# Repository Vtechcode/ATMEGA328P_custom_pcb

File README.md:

# ATMEGA328P CUSTOM PCB

A custom development board based on the ATMEGA328P chip

## Features
ATMEGA328P MCU

## Preview

## Schematic

## PCB Layout

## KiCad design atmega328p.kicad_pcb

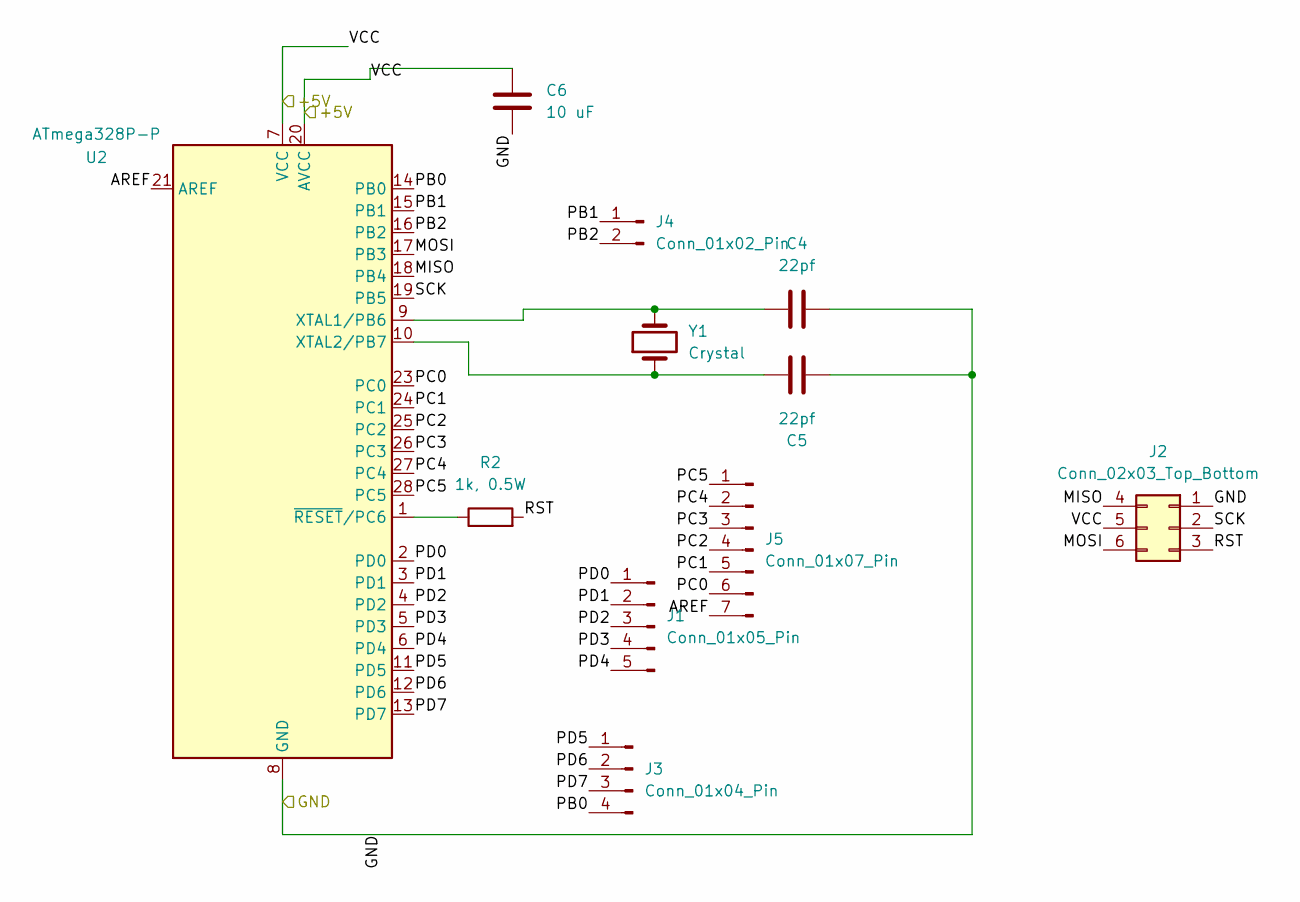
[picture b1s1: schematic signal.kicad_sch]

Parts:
C4, C5: 22pf; C_Disc_D3.8mm_W2.6mm_P2.50mm
C6: 10 uF; C_Disc_D6.0mm_W2.5mm_P5.00mm
J1: Conn_01x05_Pin; PinSocket_1x05_P2.54mm_Vertical
J2: Conn_02x03_Top_Bottom; PinSocket_2x03_P2.54mm_Vertical
J3: Conn_01x04_Pin; PinHeader_1x04_P2.54mm_Vertical
J4: Conn_01x02_Pin; PinHeader_1x02_P2.54mm_Vertical
J5: Conn_01x07_Pin; PinHeader_1x07_P2.54mm_Vertical
R2: 1k, 0.5W; R_Axial_DIN0207_L6.3mm_D2.5mm_P10.16mm_Horizontal
U2: ATmega328P-P; DIP-28_W7.62mm
Y1: Crystal; Crystal_HC18-U_Vertical

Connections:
/power/+5V: C6.1, J2.5, U2.7 (VCC), U2.20 (AVCC); also elsewhere on the board
/signal/AREF: J5.7, U2.21 (AREF)
/signal/GND: C4.2, C5.2, C6.2, J2.1, U2.8 (GND), U2.22 (GND); also elsewhere on the board
/signal/MISO: J2.4, U2.18 (PB4)
/signal/MOSI: J2.6, U2.17 (PB3)
/signal/PB0: J3.4, U2.14 (PB0)
/signal/PB1: J4.1, U2.15 (PB1)
/signal/PB2: J4.2, U2.16 (PB2)
/signal/PC0: J5.6, U2.23 (PC0)
/signal/PC1: J5.5, U2.24 (PC1)
/signal/PC2: J5.4, U2.25 (PC2)
/signal/PC3: J5.3, U2.26 (PC3)
/signal/PC4: J5.2, U2.27 (PC4)
/signal/PC5: J5.1, U2.28 (PC5)
/signal/PD0: J1.1, U2.2 (PD0)
/signal/PD1: J1.2, U2.3 (PD1)
/signal/PD2: J1.3, U2.4 (PD2)
/signal/PD3: J1.4, U2.5 (PD3)
/signal/PD4: J1.5, U2.6 (PD4)
/signal/PD5: J3.1, U2.11 (PD5)
/signal/PD6: J3.2, U2.12 (PD6)
/signal/PD7: J3.3, U2.13 (PD7)
/signal/RST: J2.3, R2.2
/signal/SCK: J2.2, U2.19 (PB5)
unnamed: C4.1, U2.9 (XTAL1/PB6), Y1.2
unnamed: C5.1, U2.10 (XTAL2/PB7), Y1.1
unnamed: R2.1, U2.1 (~RESET/PC6)

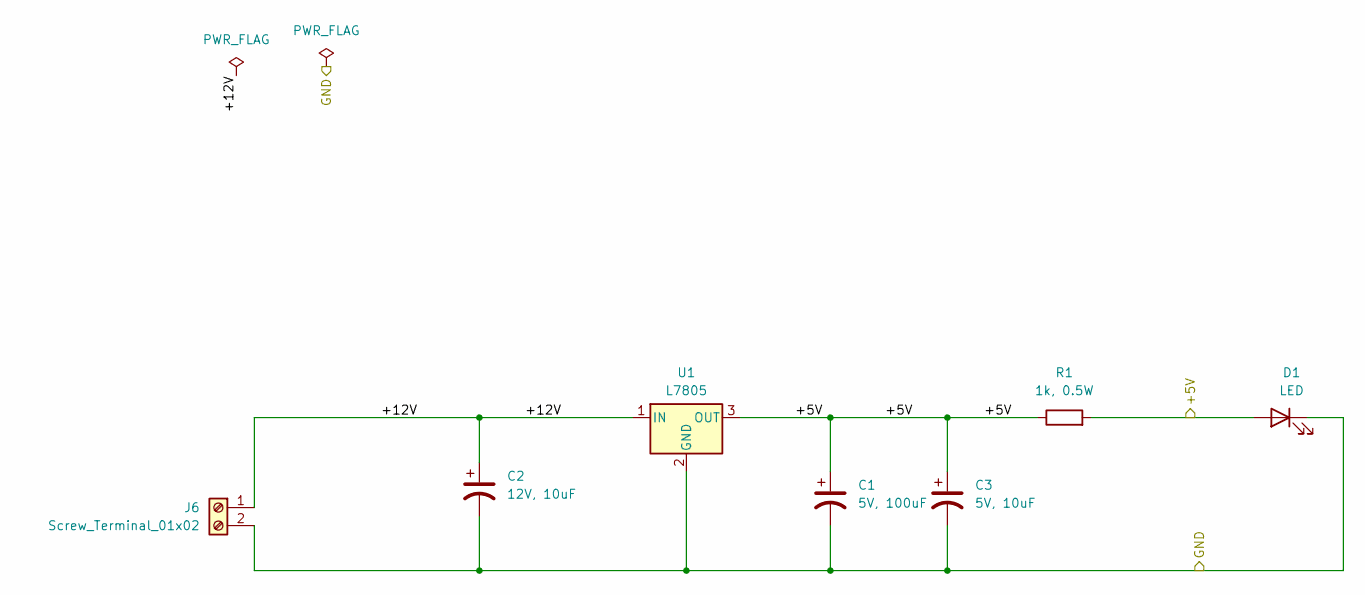
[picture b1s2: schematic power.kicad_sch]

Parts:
C1: 5V, 100uF; CP_Radial_D10.0mm_P5.00mm
C2: 12V, 10uF; CP_Radial_D10.0mm_P7.50mm
C3: 5V, 10uF; CP_Radial_D10.0mm_P7.50mm
D1: LED; LED_D5.0mm
J6: Screw_Terminal_01x02; Altech_AK300_1x02_P5.00mm_45-Degree
R1: 1k, 0.5W; R_Axial_DIN0207_L6.3mm_D2.5mm_P10.16mm_Horizontal
U1: L7805; TO-220-3_Vertical

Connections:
/power/+5V: C1.1, C3.1, D1.2 (A), R1.1, R1.2, U1.3 (OUT); also elsewhere on the board
/power/+12V: C2.1, J6.1, U1.1 (IN)
/signal/GND: C1.2, C2.2, C3.2, D1.1 (K), J6.2, U1.2 (GND); also elsewhere on the board

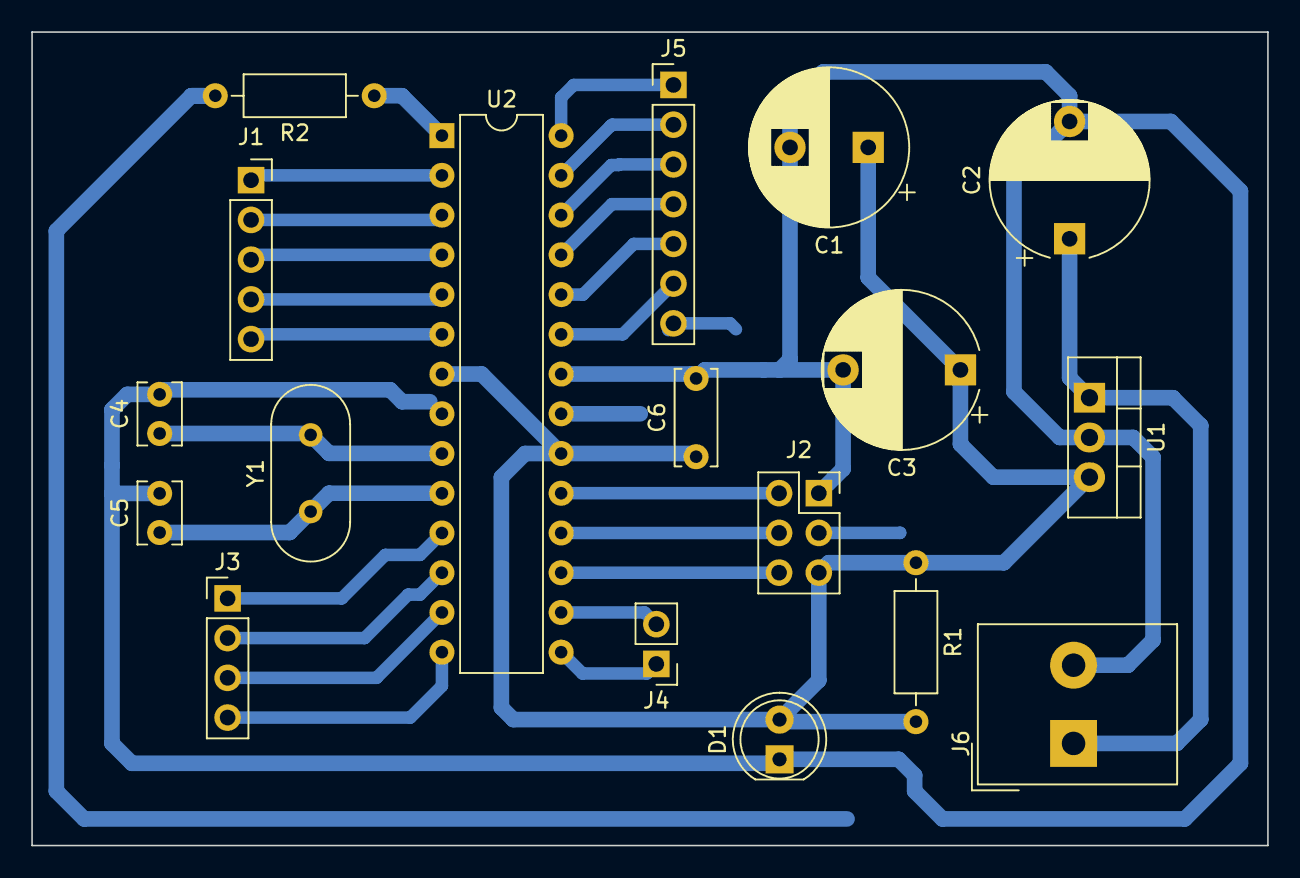
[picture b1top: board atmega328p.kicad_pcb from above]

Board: 2 copper layers, 79.0 x 52.0 mm, 18 parts (0 on the bottom side), 28 nets.

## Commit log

2025-12-05 Completed up to fabrication
2026-04-03 Added Image
